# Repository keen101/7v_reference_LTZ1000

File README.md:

# 7v_reference_LTZ1000
Ultra Precision Reference LTZ1000

This is released as Open Source / Public Domain. There is no licence.

https://keen101.wordpress.com/2013/02/12/hpagilent-03458-66509-7v-dc-reference-clone/

HP / Agilent / Keysight 03458-66509 7V DC Reference Clone

replacement boards for the HP/Agilent 3458A multimeter.  Ultra Precision DC Reference board which uses the LTZ1000.

It looks like someone else beat me to it:
https://github.com/pepaslabs/hp-03458-66509-clone

I previously released a design for the cap that goes on top:

https://www.thingiverse.com/thing:3718143

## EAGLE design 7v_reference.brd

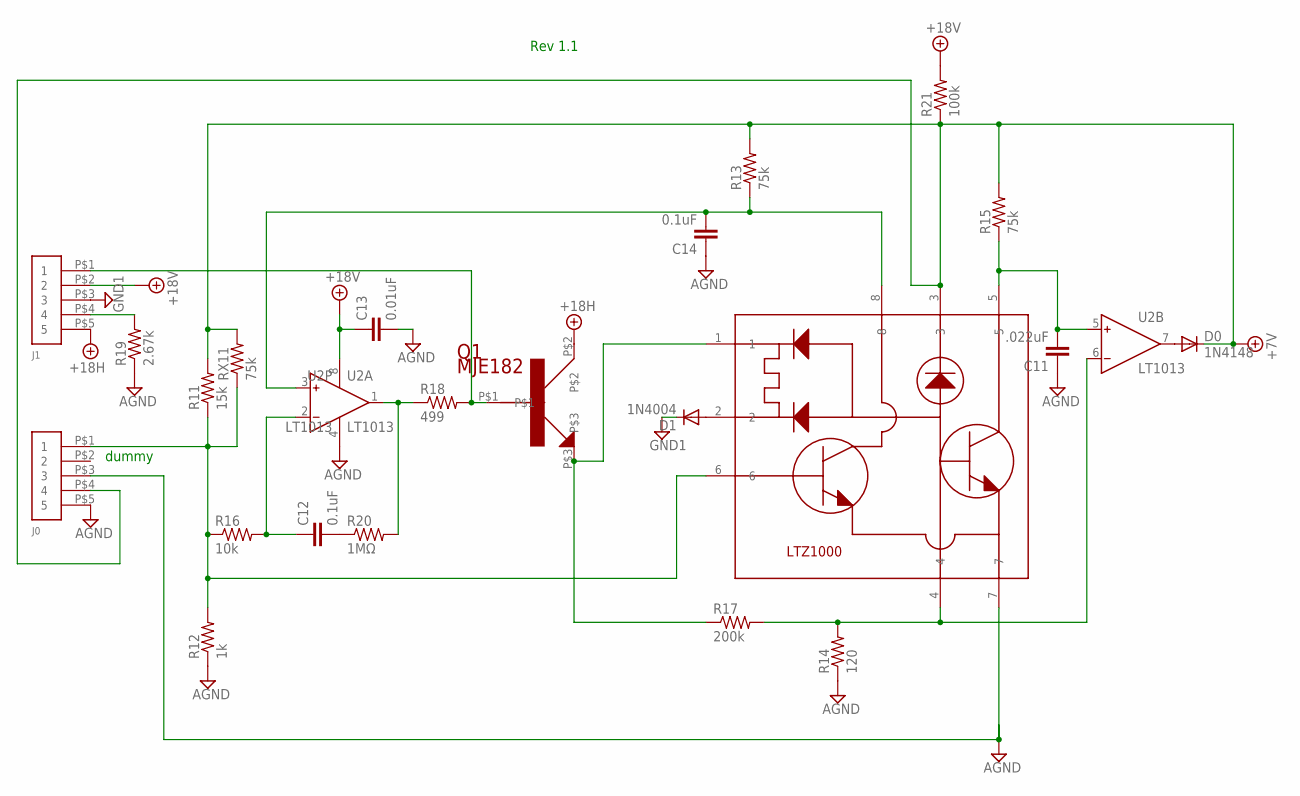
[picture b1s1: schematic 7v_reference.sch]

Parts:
C11: .022uF; C102-043X133
C12, C14: 0.1uF; C102-043X133
C13: 0.01uF; C102-043X133
D0: 1N4148; DO35-10
D1: 1N4004; DO41-10
J0: SOCKET1SOCKET1; SOCKET1
J1: SOCKET1SOCKET2; SOCKET2
Q1: MJE182; SOT-32
R11: 15k; 0411V
R12: 1k; 0411V
R13, R15: 75k; 0207/10
R14: 120; 0411V
R16: 10k; 0207/10
R17: 200k; 0207/10
R18: 499; 0207/10
R19: 2.67k; 0207/10
R20: 1MΩ; 0207/10
R21: 100k; 0207/10
RX11: 75k; 0207/10
U2: LT1013; DIL08
U$1: LTZ1000

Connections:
+7V: D0.C, J0.P$4 (4), R11.2, R13.2, R15.2, R21.1, RX11.2, U$1.3
+18V: C13.1, J1.P$2 (2), J1.P$5 (5), Q1.P$2, R21.2, U2.8 (V+)
AGND: C11.1, C13.2, C14.1, J0.P$3 (3), J0.P$5 (5), R12.1, R14.1, R19.1, U2.4 (V-), U$1.7
GND1: D1.C, J1.P$3 (3)
unnamed: C11.2, R15.1, U2.5 (IN+), U$1.5
unnamed: J1.P$1 (1), Q1.P$1, R18.2
unnamed: D1.A, U$1.2
unnamed: D0.A, U2.7 (OUT)
unnamed: J0.P$1 (1), R11.1, R12.2, R16.1, RX11.1, U$1.6
unnamed: R14.2, R17.2, U2.6 (IN-), U$1.4
unnamed: C14.2, R13.1, U2.3 (IN+), U$1.8
unnamed: R18.1, R20.2, U2.1 (OUT)
unnamed: C12.1, R16.2, U2.2 (IN-)
unnamed: C12.2, R20.1
unnamed: J1.P$4 (4), R19.2
unnamed: Q1.P$3, R17.1, U$1.1

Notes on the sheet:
dummy
Rev 1.1

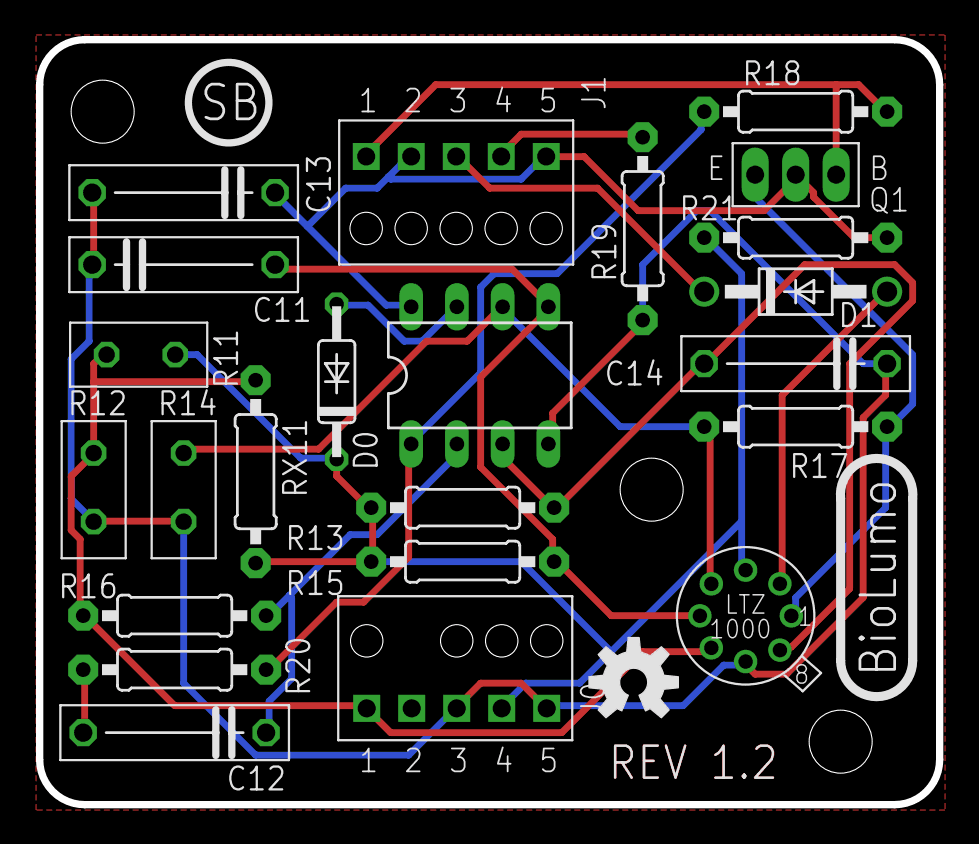
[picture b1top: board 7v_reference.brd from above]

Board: 2 copper layers, 50.0 x 42.5 mm, 24 parts (0 on the bottom side), 16 nets.

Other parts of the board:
U$2: OSHW-LOGO-M

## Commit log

2020-12-08 Add files via upload
    Added Eagle CAD files

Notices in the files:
parts and their libraries:
SparkFun-Aesthetics: Licensing: Creative Commons ShareAlike 4.0 International - https://creativecommons.org/licenses/by-sa/4.0
